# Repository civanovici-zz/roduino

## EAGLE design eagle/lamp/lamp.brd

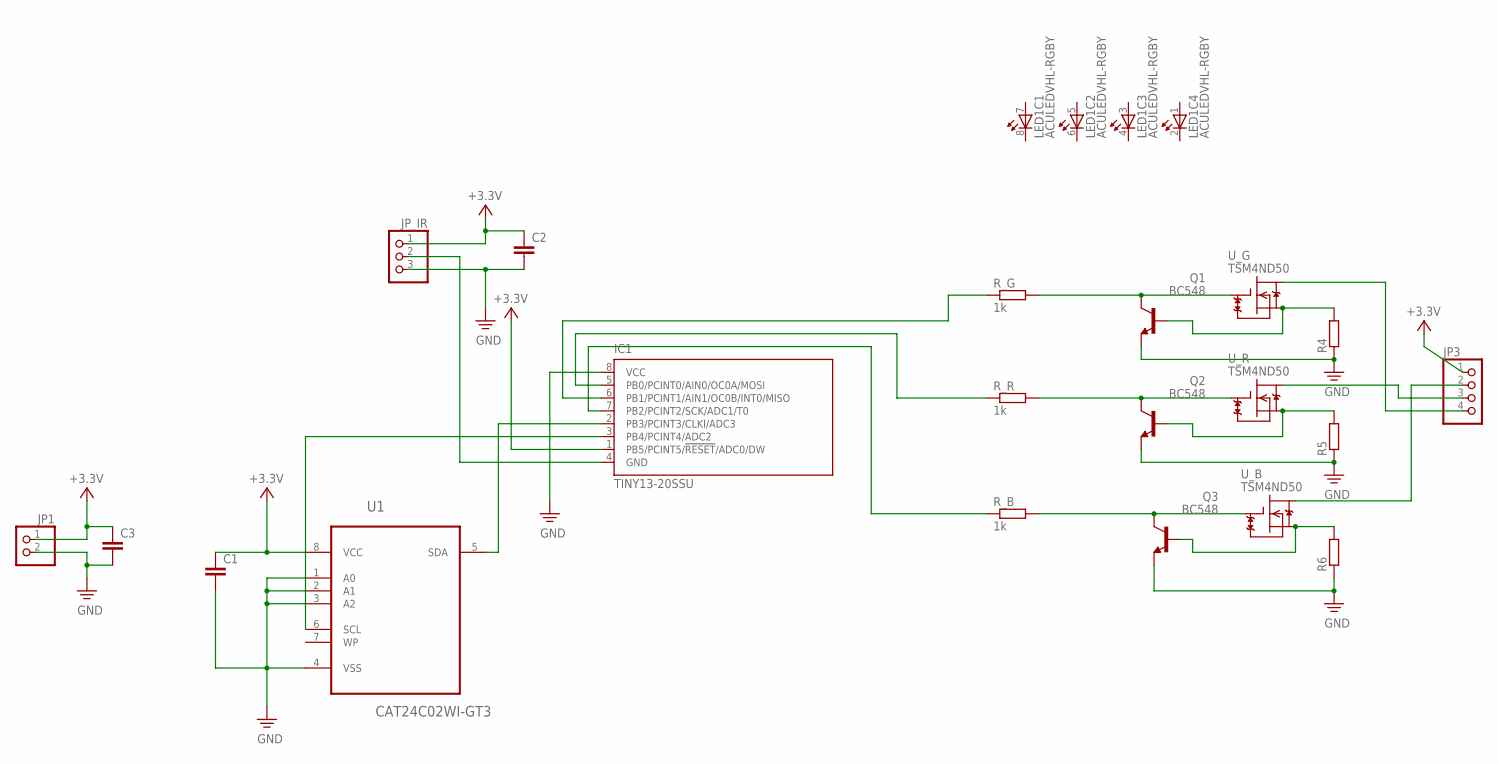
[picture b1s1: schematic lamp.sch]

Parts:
C1, C2, C3: C-EUC0805; C0805
IC1: TINY13-20SSU; 8S1
JP1: PINHD-1X2; 1X02
JP3: PINHD-1X4; 1X04
JP_IR: PINHD-1X3; 1X03
LED1: ACULEDVHL-RGBY; ACULEDVHL
Q1, Q2, Q3: BC548; TO92-EBC
R4, R5, R6: R-EU_0204/2V; 0204V
R_B: 1k; R0805
R_G: 1k; R0805
R_R: 1k; R0805
U1: CAT24C02WI-GT3; SOIC127P600X175-8N
U_B: TSM4ND50; TO252
U_G: TSM4ND50; TO252
U_R: TSM4ND50; TO252

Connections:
B: JP3.2, U_B.D
G: JP3.4, U_G.D
unnamed: IC1.2 (PB3/PCINT3/CLKI/ADC3), U1.5 (SDA)
unnamed: IC1.3 (PB4/PCINT4/ADC2), U1.6 (SCL)
unnamed: IC1.4 (GND), JP_IR.2
unnamed: Q1.C, R_G.2, U_G.G
unnamed: IC1.7 (PB2/PCINT2/SCK/ADC1/T0), R_B.1
unnamed: IC1.5 (PB0/PCINT0/AIN0/OC0A/MOSI), R_R.1
unnamed: IC1.6 (PB1/PCINT1/AIN1/OC0B/INT0/MISO), R_G.1
unnamed: Q1.B, R4.2, U_G.S
unnamed: Q2.C, R_R.2, U_R.G
unnamed: Q2.B, R5.2, U_R.S
unnamed: Q3.C, R_B.2, U_B.G
unnamed: Q3.B, R6.2, U_B.S
PE: C1.2, C2.2, C3.2, IC1.8 (VCC), JP1.2, JP_IR.3, Q1.E, Q2.E, Q3.E, R4.1, R5.1, R6.1, U1.1 (A0), U1.2 (A1), U1.3 (A2), U1.4 (VSS)
R: JP3.3, U_R.D
VCC: C1.1, C2.1, C3.1, IC1.1 (PB5/PCINT5/!RESET!/ADC0/DW), JP1.1, JP3.1, JP_IR.1, U1.8 (VCC)

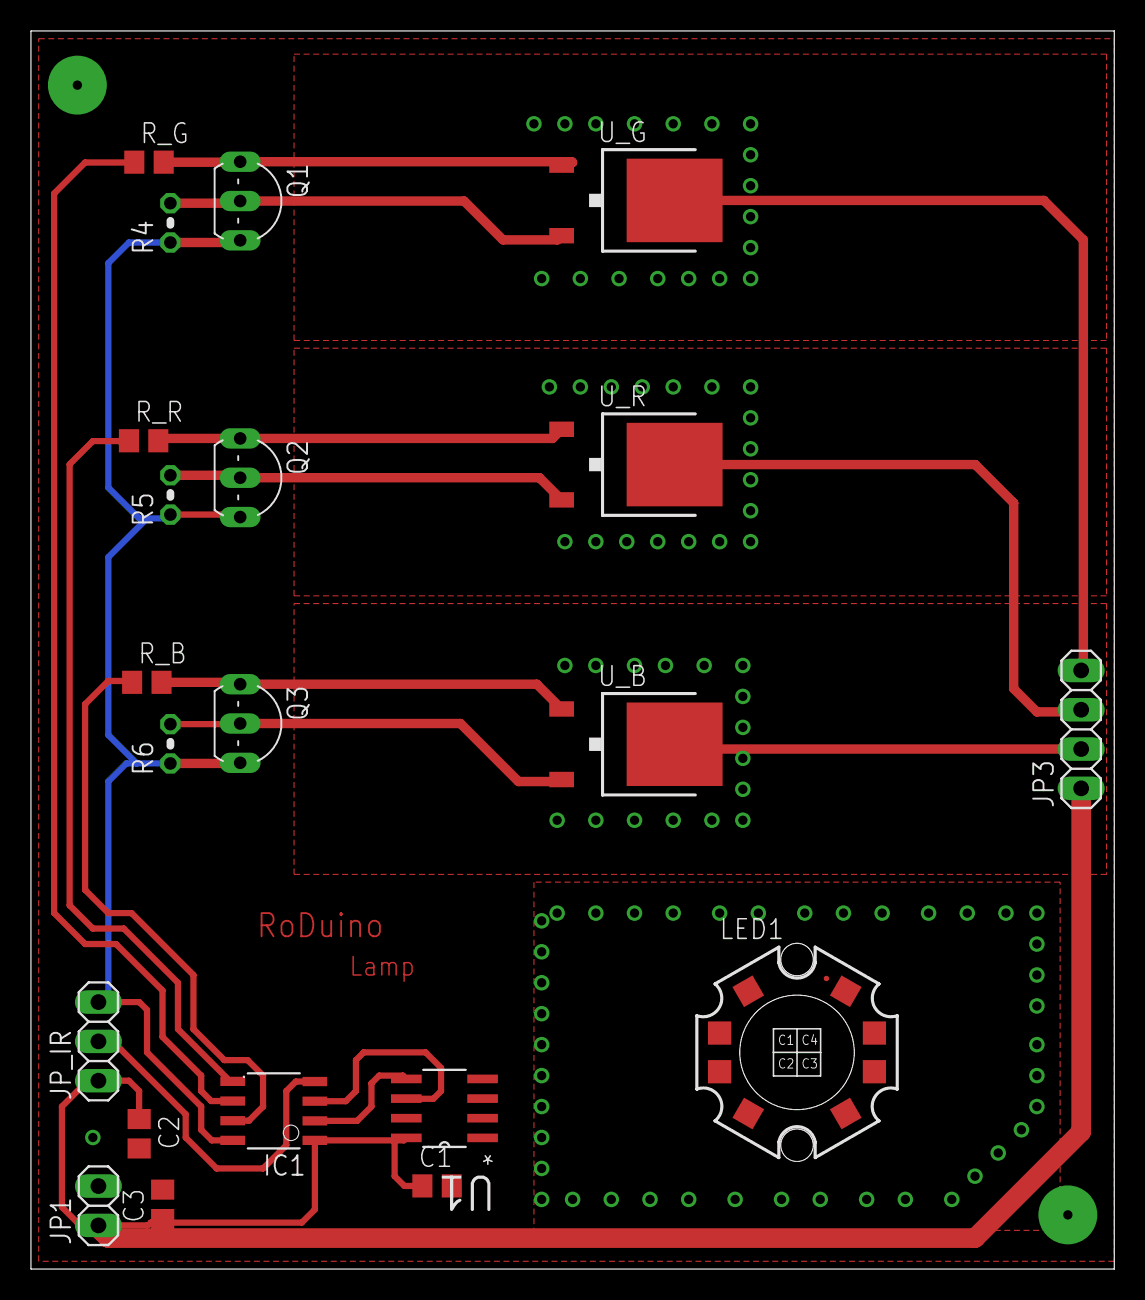
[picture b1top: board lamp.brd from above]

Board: 2 copper layers, 70.0 x 80.0 mm, 21 parts (0 on the bottom side), 17 nets.

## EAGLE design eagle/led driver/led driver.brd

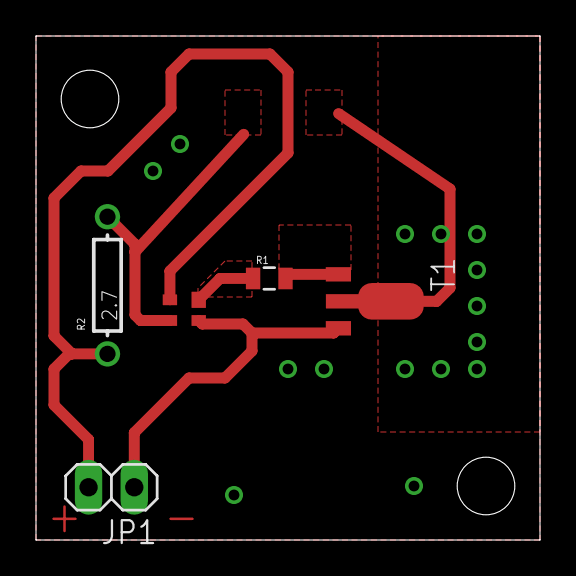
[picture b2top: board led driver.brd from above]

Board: 2 copper layers, 28.0 x 28.0 mm, 5 parts (0 on the bottom side), 5 nets.

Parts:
JP1: 1X02
R1: 220; 0805
R2: 2.7; AXIAL-0.3
T1: SOT89-BCE
U$9: BCR401W; SOT-343

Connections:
3.3V: JP1.2, R2.P$1, U$9.VSS
GND: JP1.1, T1.E, U$9.GND
unnamed: R1.2, T1.B
unnamed: R1.1, U$9.IOUT
unnamed: R2.P$2, U$9.REXT

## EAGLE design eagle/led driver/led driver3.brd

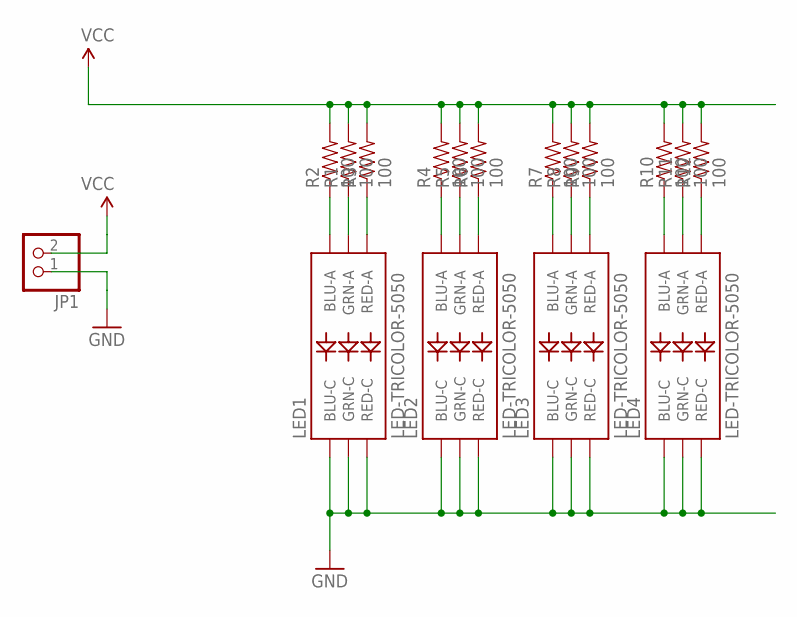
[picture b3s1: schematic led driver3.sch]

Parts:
JP1: PINHD-1X2; 1X02
LED1, LED2, LED3, LED4: LED-TRICOLOR-5050
R1, R2, R3, R4, R5, R6, R7, R8, R9, R10, R11, R12: 100; 0603-RES

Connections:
GND: JP1.1, LED1.4 (BLU-C), LED1.5 (RED-C), LED1.6 (GRN-C), LED2.4 (BLU-C), LED2.5 (RED-C), LED2.6 (GRN-C), LED3.4 (BLU-C), LED3.5 (RED-C), LED3.6 (GRN-C), LED4.4 (BLU-C), LED4.5 (RED-C), LED4.6 (GRN-C)
unnamed: LED2.3 (BLU-A), R4.1
unnamed: LED2.1 (GRN-A), R5.1
unnamed: LED2.2 (RED-A), R6.1
unnamed: LED3.3 (BLU-A), R7.1
unnamed: LED3.1 (GRN-A), R8.1
unnamed: LED3.2 (RED-A), R9.1
unnamed: LED4.3 (BLU-A), R10.1
unnamed: LED4.1 (GRN-A), R11.1
unnamed: LED4.2 (RED-A), R12.1
unnamed: LED1.3 (BLU-A), R2.1
unnamed: LED1.1 (GRN-A), R1.1
unnamed: LED1.2 (RED-A), R3.1
VCC: JP1.2, R1.2, R2.2, R3.2, R4.2, R5.2, R6.2, R7.2, R8.2, R9.2, R10.2, R11.2, R12.2

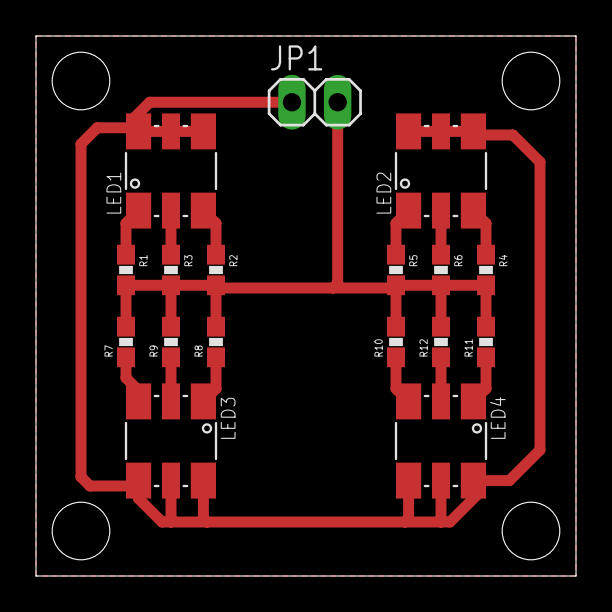
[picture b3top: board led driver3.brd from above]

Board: 2 copper layers, 30.0 x 30.0 mm, 17 parts (0 on the bottom side), 14 nets.

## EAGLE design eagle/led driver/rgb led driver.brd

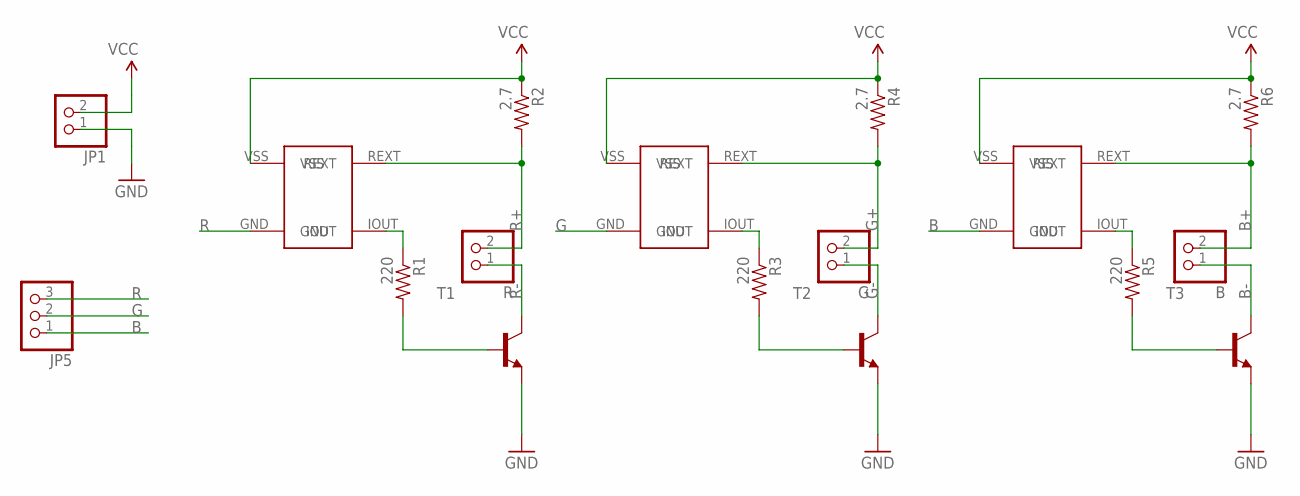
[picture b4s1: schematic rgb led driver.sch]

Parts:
B: PINHD-1X2; 1X02
G: PINHD-1X2; 1X02
JP1: PINHD-1X2; 1X02
JP5: PINHD-1X3; 1X03
R: PINHD-1X2; 1X02
R1, R3, R5: 220; 0805
R2, R4, R6: 2.7; AXIAL-0.3
T1, T2, T3: -NPN-SOT89-BCE; SOT89-BCE
U$1, U$2, U$9: BCR401W; SOT-343

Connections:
3.3V: JP1.2, R2.P$1 (1), R4.P$1 (1), R6.P$1 (1), U$1.VSS, U$2.VSS, U$9.VSS
B: JP5.1, U$2.GND
B+: B.2, R6.P$2 (2), U$2.REXT
B-: B.1, T3.C
G: JP5.2, U$1.GND
G+: G.2, R4.P$2 (2), U$1.REXT
G-: G.1, T2.C
GND: JP1.1, T1.E, T2.E, T3.E
unnamed: R1.2, T1.B
unnamed: R3.1, U$1.IOUT
unnamed: R3.2, T2.B
unnamed: R5.1, U$2.IOUT
unnamed: R5.2, T3.B
unnamed: R1.1, U$9.IOUT
R: JP5.3, U$9.GND
R+: R.2, R2.P$2 (2), U$9.REXT
R-: R.1, T1.C

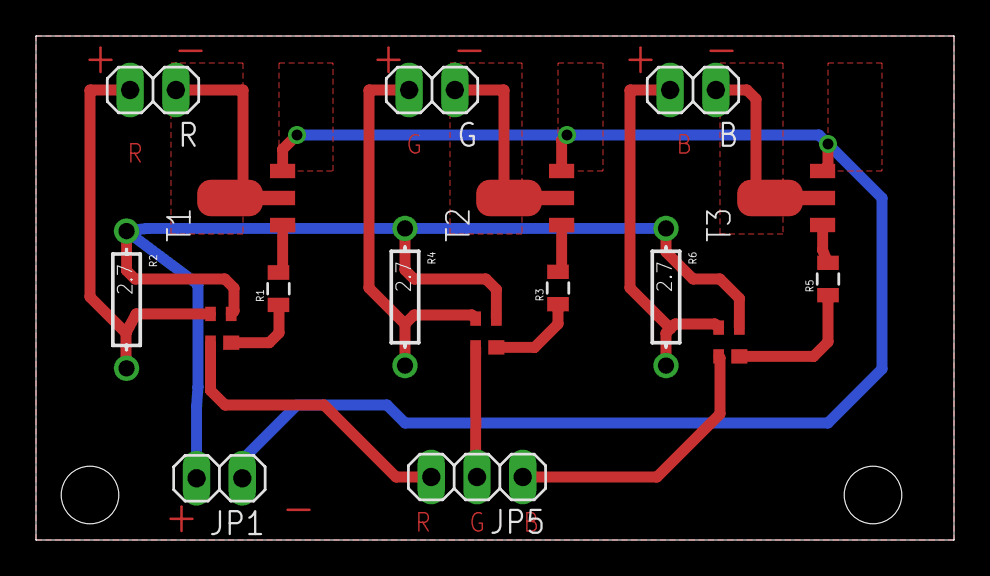
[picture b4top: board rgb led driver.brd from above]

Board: 2 copper layers, 51.0 x 28.0 mm, 17 parts (0 on the bottom side), 17 nets.

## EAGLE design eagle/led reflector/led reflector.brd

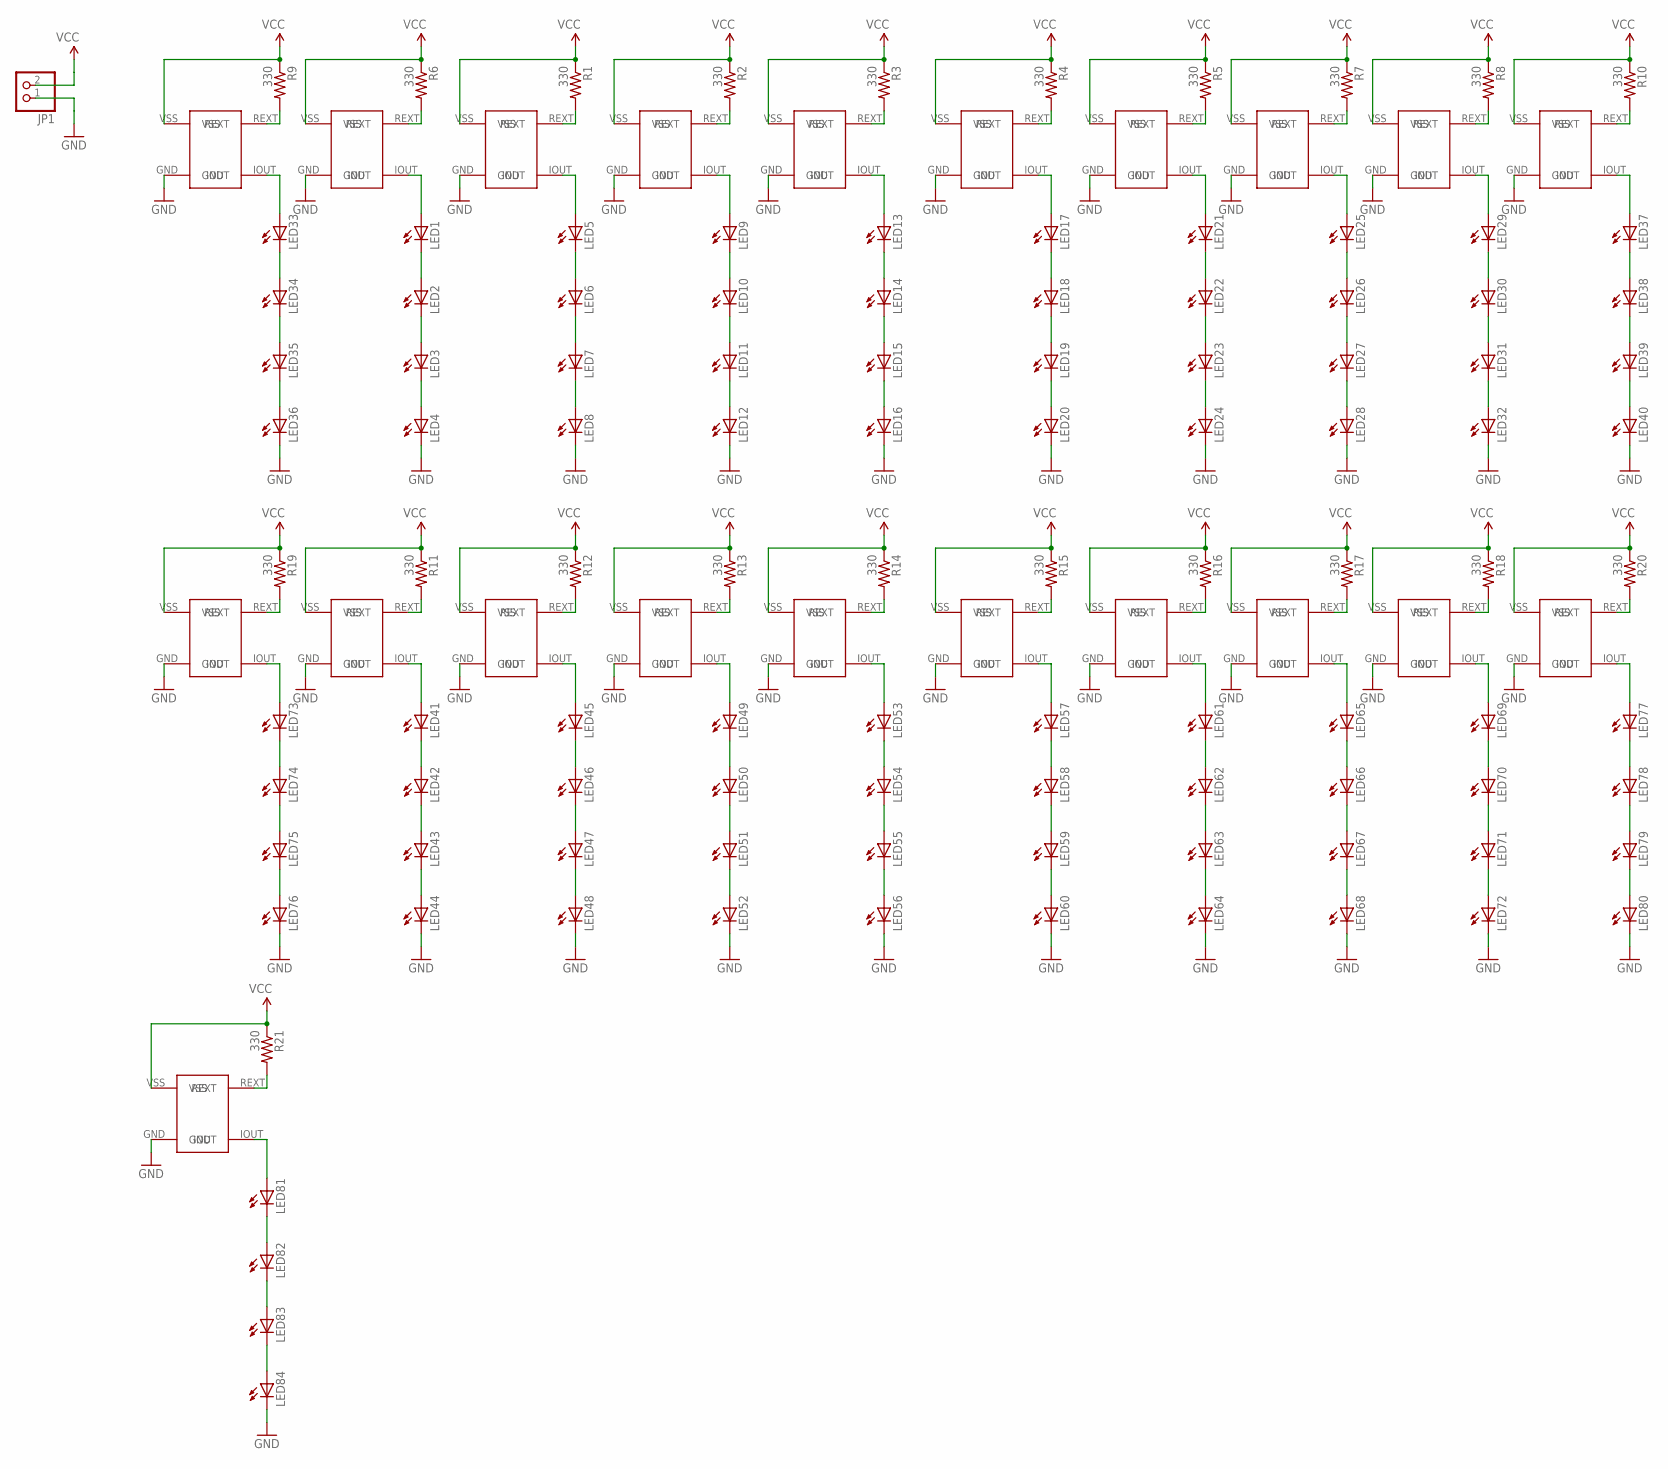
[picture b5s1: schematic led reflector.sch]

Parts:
JP1: PINHD-1X2; 1X02
LED1, LED2, LED3, LED4, LED5, LED6, LED7, LED8, LED9, LED10, LED11, LED12, LED13, LED14, LED15, LED16, LED17, LED18, LED19, LED20, LED21, LED22, LED23, LED24, LED25, LED26, LED27, LED28, LED29, LED30, LED31, LED32, LED33, LED34, LED35, LED36, LED37, LED38, LED39, LED40, LED41, LED42, LED43, LED44, LED45, LED46, LED47, LED48, LED49, LED50, LED51, LED52, LED53, LED54, LED55, LED56, LED57, LED58, LED59, LED60, LED61, LED62, LED63, LED64, LED65, LED66, LED67, LED68, LED69, LED70, LED71, LED72, LED73, LED74, LED75, LED76, LED77, LED78, LED79, LED80, LED81, LED82, LED83, LED84: LED5MM
R1, R2, R3, R4, R5, R6, R7, R8, R9, R10, R11, R12, R13, R14, R15, R16, R17, R18, R19, R20, R21: 330; 0805
U$1, U$2, U$3, U$4, U$5, U$6, U$7, U$8, U$9, U$10, U$11, U$12, U$13, U$14, U$15, U$16, U$17, U$18, U$19, U$20, U$21: BCR401W; SOT-343

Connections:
3.3V: JP1.2, R1.1, R2.1, R3.1, R4.1, R5.1, R6.1, R7.1, R8.1, R9.1, R10.1, R11.1, R12.1, R13.1, R14.1, R15.1, R16.1, R17.1, R18.1, R19.1, R20.1, R21.1, U$1.VSS, U$2.VSS, U$3.VSS, U$4.VSS, U$5.VSS, U$6.VSS, U$7.VSS, U$8.VSS, U$9.VSS, U$10.VSS, U$11.VSS, U$12.VSS, U$13.VSS, U$14.VSS, U$15.VSS, U$16.VSS, U$17.VSS, U$18.VSS, U$19.VSS, U$20.VSS, U$21.VSS
GND: JP1.1, LED4.K (C), LED8.K (C), LED12.K (C), LED16.K (C), LED20.K (C), LED24.K (C), LED28.K (C), LED32.K (C), LED36.K (C), LED40.K (C), LED44.K (C), LED48.K (C), LED52.K (C), LED56.K (C), LED60.K (C), LED64.K (C), LED68.K (C), LED72.K (C), LED76.K (C), LED80.K (C), LED84.K (C), U$1.GND, U$2.GND, U$3.GND, U$4.GND, U$5.GND, U$6.GND, U$7.GND, U$8.GND, U$9.GND, U$10.GND, U$11.GND, U$12.GND, U$13.GND, U$14.GND, U$15.GND, U$16.GND, U$17.GND, U$18.GND, U$19.GND, U$20.GND, U$21.GND
unnamed: LED1.A, U$1.IOUT
unnamed: LED1.K (C), LED2.A
unnamed: LED2.K (C), LED3.A
unnamed: LED3.K (C), LED4.A
unnamed: R6.2, U$1.REXT
unnamed: LED41.A, U$11.IOUT
unnamed: LED5.A, U$2.IOUT
unnamed: LED5.K (C), LED6.A
unnamed: LED6.K (C), LED7.A
unnamed: LED7.K (C), LED8.A
unnamed: R1.2, U$2.REXT
unnamed: LED9.A, U$3.IOUT
unnamed: LED9.K (C), LED10.A
unnamed: LED10.K (C), LED11.A
unnamed: LED11.K (C), LED12.A
unnamed: R2.2, U$3.REXT
unnamed: LED13.A, U$4.IOUT
unnamed: LED13.K (C), LED14.A
unnamed: LED14.K (C), LED15.A
unnamed: LED15.K (C), LED16.A
unnamed: R3.2, U$4.REXT
unnamed: LED17.A, U$5.IOUT
unnamed: LED17.K (C), LED18.A
unnamed: LED18.K (C), LED19.A
unnamed: LED19.K (C), LED20.A
unnamed: R4.2, U$5.REXT
unnamed: LED21.A, U$6.IOUT
unnamed: LED21.K (C), LED22.A
unnamed: LED22.K (C), LED23.A
unnamed: LED23.K (C), LED24.A
unnamed: R5.2, U$6.REXT
unnamed: LED25.A, U$7.IOUT
unnamed: LED25.K (C), LED26.A
unnamed: LED26.K (C), LED27.A
unnamed: LED27.K (C), LED28.A
unnamed: R7.2, U$7.REXT
unnamed: LED29.A, U$8.IOUT
unnamed: LED29.K (C), LED30.A
unnamed: LED30.K (C), LED31.A
unnamed: LED31.K (C), LED32.A
unnamed: R8.2, U$8.REXT
unnamed: LED33.A, U$9.IOUT
unnamed: LED33.K (C), LED34.A
unnamed: LED34.K (C), LED35.A
unnamed: LED35.K (C), LED36.A
unnamed: R9.2, U$9.REXT
unnamed: LED37.A, U$10.IOUT
unnamed: LED37.K (C), LED38.A
unnamed: LED38.K (C), LED39.A
unnamed: LED39.K (C), LED40.A
unnamed: R10.2, U$10.REXT
unnamed: LED41.K (C), LED42.A
unnamed: LED42.K (C), LED43.A
unnamed: LED43.K (C), LED44.A
unnamed: R11.2, U$11.REXT
unnamed: LED45.A, U$12.IOUT
unnamed: LED45.K (C), LED46.A
unnamed: LED46.K (C), LED47.A
unnamed: LED47.K (C), LED48.A
unnamed: R12.2, U$12.REXT
unnamed: LED49.A, U$13.IOUT
unnamed: LED49.K (C), LED50.A
unnamed: LED50.K (C), LED51.A
unnamed: LED51.K (C), LED52.A
unnamed: R13.2, U$13.REXT
unnamed: LED53.A, U$14.IOUT
unnamed: LED53.K (C), LED54.A
unnamed: LED54.K (C), LED55.A
unnamed: LED55.K (C), LED56.A
unnamed: R14.2, U$14.REXT
unnamed: LED57.A, U$15.IOUT
unnamed: LED57.K (C), LED58.A
unnamed: LED58.K (C), LED59.A
unnamed: LED59.K (C), LED60.A
unnamed: R15.2, U$15.REXT
unnamed: LED61.A, U$16.IOUT
unnamed: LED61.K (C), LED62.A
unnamed: LED62.K (C), LED63.A
unnamed: LED63.K (C), LED64.A
unnamed: R16.2, U$16.REXT
unnamed: LED65.A, U$17.IOUT
unnamed: LED65.K (C), LED66.A
unnamed: LED66.K (C), LED67.A
unnamed: LED67.K (C), LED68.A
unnamed: R17.2, U$17.REXT
unnamed: LED69.A, U$18.IOUT
unnamed: LED69.K (C), LED70.A
unnamed: LED70.K (C), LED71.A
unnamed: LED71.K (C), LED72.A
unnamed: R18.2, U$18.REXT
unnamed: LED73.A, U$19.IOUT
unnamed: LED73.K (C), LED74.A
unnamed: LED74.K (C), LED75.A
unnamed: LED75.K (C), LED76.A
unnamed: R19.2, U$19.REXT
unnamed: LED77.A, U$20.IOUT
unnamed: LED77.K (C), LED78.A
unnamed: LED78.K (C), LED79.A
unnamed: LED79.K (C), LED80.A
unnamed: R20.2, U$20.REXT
unnamed: LED81.A, U$21.IOUT
unnamed: LED81.K (C), LED82.A
unnamed: LED82.K (C), LED83.A
unnamed: LED83.K (C), LED84.A
unnamed: R21.2, U$21.REXT

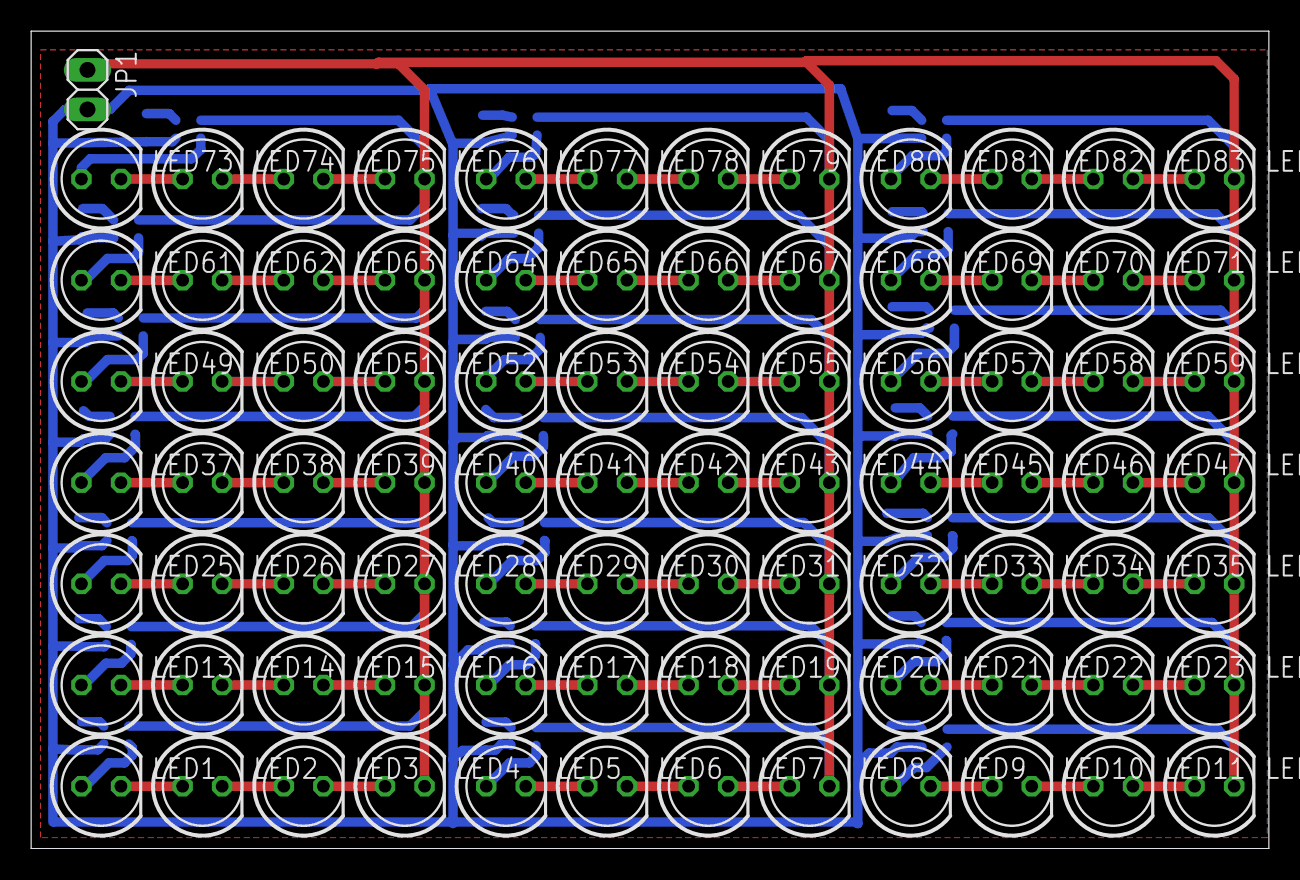
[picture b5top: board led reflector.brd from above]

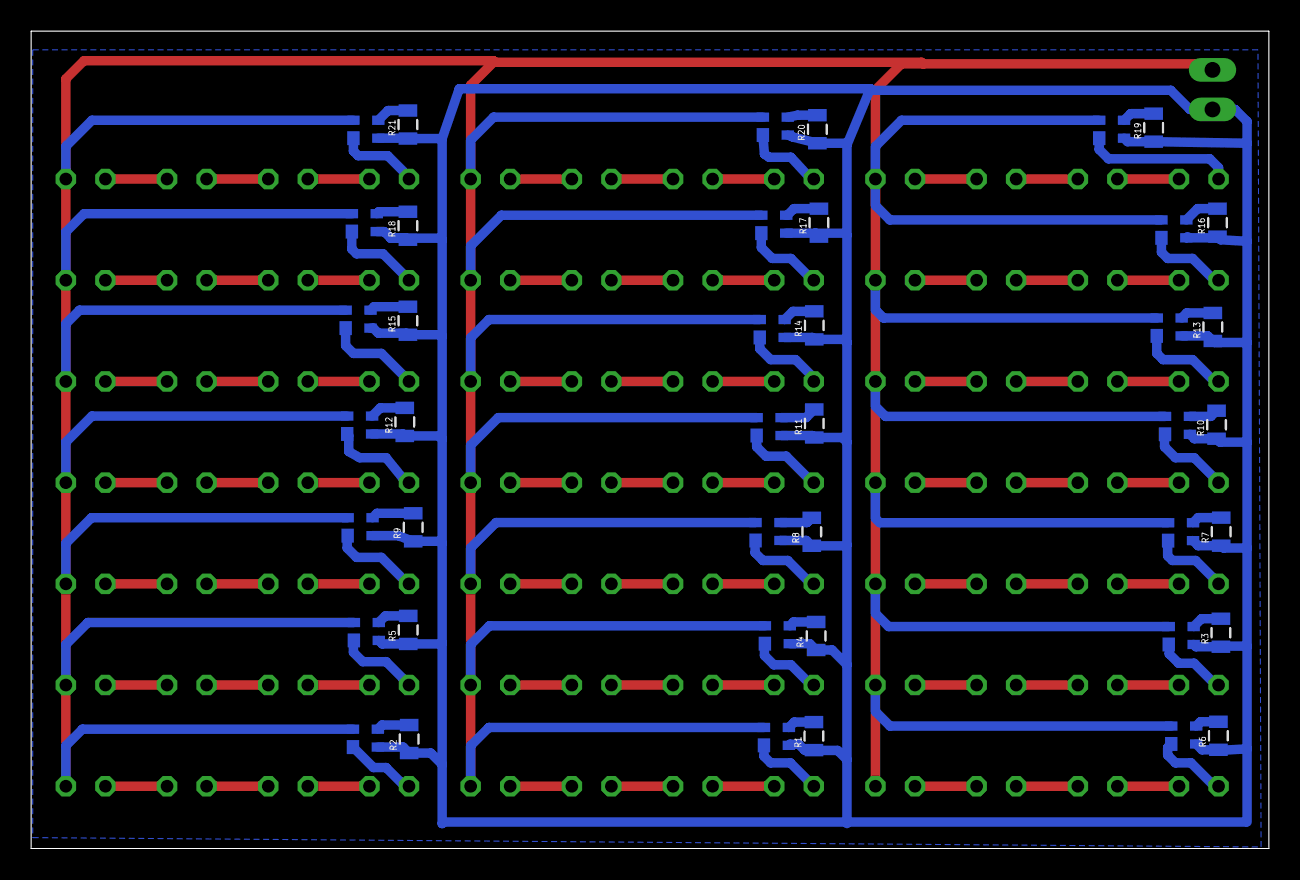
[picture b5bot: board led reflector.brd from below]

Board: 2 copper layers, 79.5 x 52.5 mm, 127 parts (42 on the bottom side), 107 nets.

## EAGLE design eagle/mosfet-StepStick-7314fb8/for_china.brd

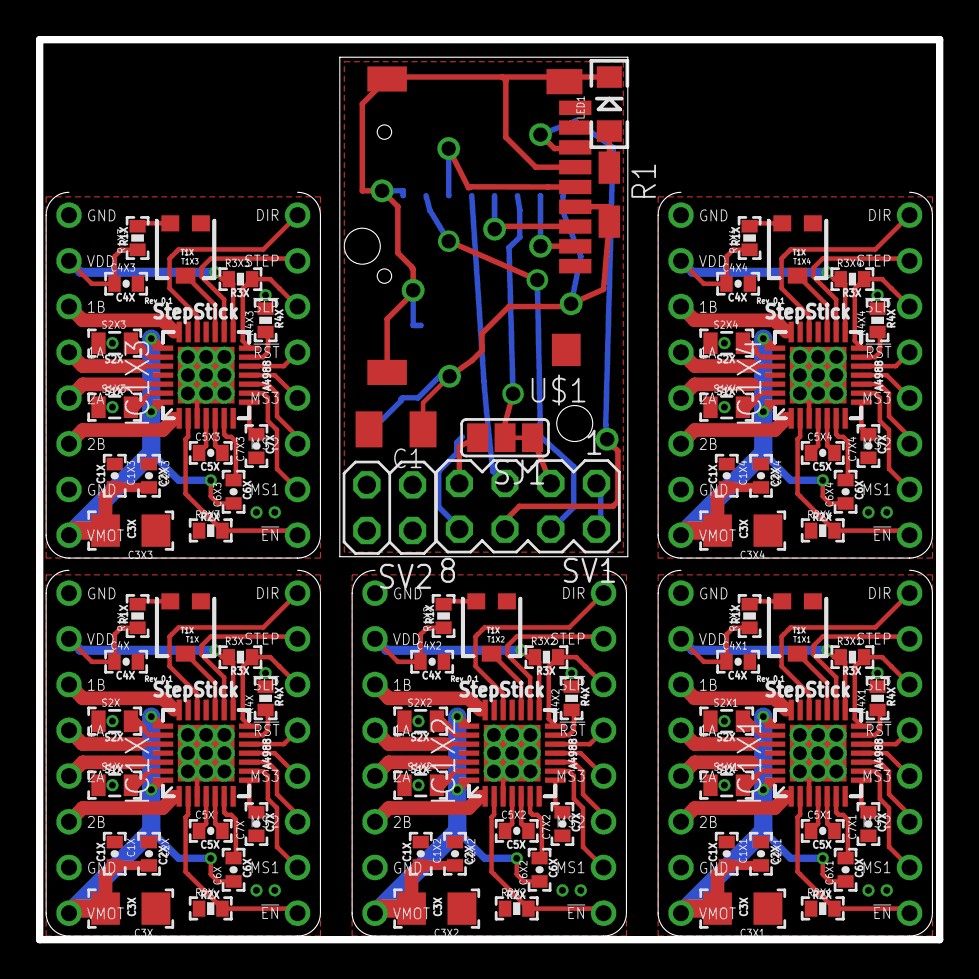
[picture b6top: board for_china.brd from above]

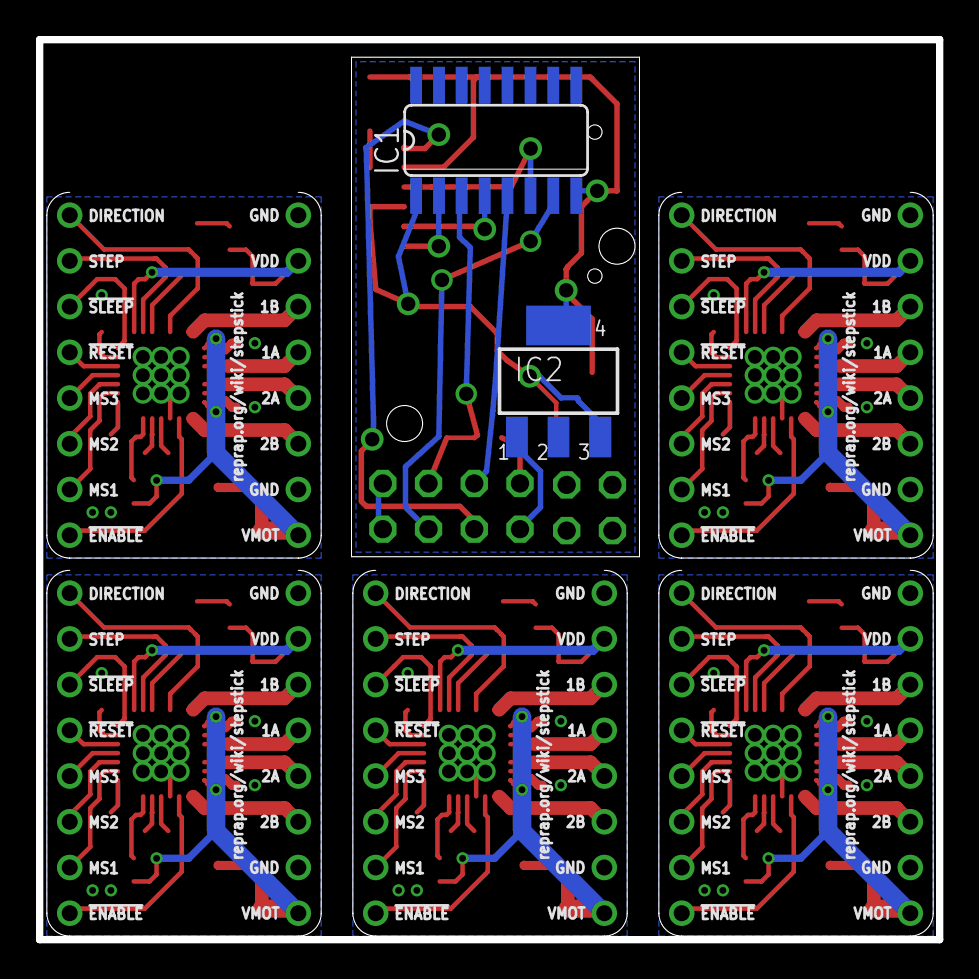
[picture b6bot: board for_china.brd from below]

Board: 2 copper layers, 50.0 x 50.0 mm, 89 parts (2 on the bottom side), 132 nets.

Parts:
C1: C1206K
C1X, C1X1, C1X2, C1X3, C1X4, C2X, C2X1, C2X2, C2X3, C2X4, C5X, C5X1, C5X2, C5X3, C5X4, C6X, C6X1, C6X2, C6X3, C6X4: .1uf; 0402-CAP
C3X, C3X1, C3X2, C3X3, C3X4: 4.7uF; 1206
C4X, C4X1, C4X2, C4X3, C4X4, C7X, C7X1, C7X2, C7X3, C7X4: .22uf; 0402-CAP
IC1: 4050D; SO16
IC1X, IC1X1, IC1X2, IC1X3, IC1X4: A4988; QFN28ET
IC2: LM340MP-05; SOT223
J1X, J1X1, J1X2, J1X3, J1X4: CLONOLU
LED1: LED-1206
R1: R1206W
R1X, R1X1, R1X2, R1X3, R1X4: 20k; 0402-RES
R2X, R2X1, R2X2, R2X3, R2X4, R3X, R3X1, R3X2, R3X3, R3X4: 100k; 0402-RES
R4X, R4X1, R4X2, R4X3, R4X4: 10k; 0402-RES
S1X, S1X1, S1X2, S1X3, S1X4, S2X, S2X1, S2X2, S2X3, S2X4: 0.2; 0805
SJ1: SJ_2
SV1: MA04-2
SV2: 2X02
T1X, T1X1, T1X2, T1X3, T1X4: TRIM; TRIMPOT-3MM
U$1: MICROSD_PP

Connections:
GND: C1X.1, C2X.1, C3X.1, C4X.2, C7X.1, IC1X.3, IC1X.7, IC1X.18, IC1X.20, IC1X.25, IC1X.EXP, J1X.GND$1, J1X.GND$2, R2X.1, R4X.2, S1X.1, S2X.1, T1X.1
GND1: C1X1.1, C2X1.1, C3X1.1, C4X1.2, C7X1.1, IC1X1.3, IC1X1.7, IC1X1.18, IC1X1.20, IC1X1.25, IC1X1.EXP, J1X1.GND$1, J1X1.GND$2, R2X1.1, R4X1.2, S1X1.1, S2X1.1, T1X1.1
GND2: C1X2.1, C2X2.1, C3X2.1, C4X2.2, C7X2.1, IC1X2.3, IC1X2.7, IC1X2.18, IC1X2.20, IC1X2.25, IC1X2.EXP, J1X2.GND$1, J1X2.GND$2, R2X2.1, R4X2.2, S1X2.1, S2X2.1, T1X2.1
GND3: C1X3.1, C2X3.1, C3X3.1, C4X3.2, C7X3.1, IC1X3.3, IC1X3.7, IC1X3.18, IC1X3.20, IC1X3.25, IC1X3.EXP, J1X3.GND$1, J1X3.GND$2, R2X3.1, R4X3.2, S1X3.1, S2X3.1, T1X3.1
GND4: C1.2, IC1.8, IC2.4, LED1.C, SV1.1, SV1.2, U$1.6, U$1.GND@1, U$1.GND@2, U$1.GND@3, U$1.GND@4
GND5: C1X4.1, C2X4.1, C3X4.1, C4X4.2, C7X4.1, IC1X4.3, IC1X4.7, IC1X4.18, IC1X4.20, IC1X4.25, IC1X4.EXP, J1X4.GND$1, J1X4.GND$2, R2X4.1, R4X4.2, S1X4.1, S2X4.1, T1X4.1
unnamed: IC1.2, U$1.2
unnamed: IC1.4, U$1.3
unnamed: IC1.6, U$1.5
unnamed: SV1.6, U$1.7
unnamed: SJ1.3, SV1.7
unnamed: IC1.3, SJ1.1, SJ1.2, SV1.3
unnamed: IC1.7, SV1.4
unnamed: IC1.5, SV1.5
unnamed: IC2.1, SV1.8
unnamed: LED1.A, R1.1
VCC: C1.1, IC1.1, IC2.3, R1.2, U$1.4
VDD: C4X.1, IC1X.15, J1X.VDD, R1X.1, R3X.1
VDD1: C4X1.1, IC1X1.15, J1X1.VDD, R1X1.1, R3X1.1
VDD2: C4X2.1, IC1X2.15, J1X2.VDD, R1X2.1, R3X2.1
VDD3: C4X3.1, IC1X3.15, J1X3.VDD, R1X3.1, R3X3.1
VDD4: C4X4.1, IC1X4.15, J1X4.VDD, R1X4.1, R3X4.1
VMOT: C1X.2, C2X.2, C3X.2, C6X.1, IC1X.22, IC1X.28, J1X.VMOT
VMOT1: C1X1.2, C2X1.2, C3X1.2, C6X1.1, IC1X1.22, IC1X1.28, J1X1.VMOT
VMOT2: C1X2.2, C2X2.2, C3X2.2, C6X2.1, IC1X2.22, IC1X2.28, J1X2.VMOT
VMOT3: C1X3.2, C2X3.2, C3X3.2, C6X3.1, IC1X3.22, IC1X3.28, J1X3.VMOT
VMOT4: C1X4.2, C2X4.2, C3X4.2, C6X4.1, IC1X4.22, IC1X4.28, J1X4.VMOT
XCP1: C5X.1, IC1X.4
XCP2: C5X.2, IC1X.5
XCP3: C5X1.1, IC1X1.4
XCP4: C5X1.2, IC1X1.5
XCP5: C5X2.1, IC1X2.4
XCP6: C5X2.2, IC1X2.5
XCP7: C5X3.1, IC1X3.4
XCP8: C5X3.2, IC1X3.5
XCP9: C5X4.1, IC1X4.4
XCP10: C5X4.2, IC1X4.5
XDIR: IC1X.19, J1X.DIR
XDIR1: IC1X1.19, J1X1.DIR
XDIR2: IC1X2.19, J1X2.DIR
XDIR3: IC1X3.19, J1X3.DIR
XDIR4: IC1X4.19, J1X4.DIR
XENABLE: IC1X.2, J1X.!EN, R2X.2
XENABLE1: IC1X1.2, J1X1.!EN, R2X1.2
XENABLE2: IC1X2.2, J1X2.!EN, R2X2.2
XENABLE3: IC1X3.2, J1X3.!EN, R2X3.2
XENABLE4: IC1X4.2, J1X4.!EN, R2X4.2
XMS1: IC1X.9, J1X.MS1
XMS2: IC1X.10, J1X.MS2
XMS3: IC1X.11, J1X.MS3
XMS4: IC1X1.9, J1X1.MS1
XMS5: IC1X1.10, J1X1.MS2
XMS6: IC1X1.11, J1X1.MS3
XMS7: IC1X2.9, J1X2.MS1
XMS8: IC1X2.10, J1X2.MS2
XMS9: IC1X2.11, J1X2.MS3
XMS10: IC1X3.9, J1X3.MS1
XMS11: IC1X3.10, J1X3.MS2
XMS12: IC1X3.11, J1X3.MS3
XMS13: IC1X4.9, J1X4.MS1
XMS14: IC1X4.10, J1X4.MS2
XMS15: IC1X4.11, J1X4.MS3
XOUT1A: IC1X.24, J1X.1A
XOUT1A1: IC1X1.24, J1X1.1A
XOUT1A2: IC1X2.24, J1X2.1A
XOUT1A3: IC1X3.24, J1X3.1A
XOUT1A4: IC1X4.24, J1X4.1A
XOUT1B: IC1X.21, J1X.1B
XOUT1B1: IC1X1.21, J1X1.1B
XOUT1B2: IC1X2.21, J1X2.1B
XOUT1B3: IC1X3.21, J1X3.1B
XOUT1B4: IC1X4.21, J1X4.1B
XOUT2A: IC1X.26, J1X.2A
XOUT2A1: IC1X1.26, J1X1.2A
XOUT2A2: IC1X2.26, J1X2.2A
XOUT2A3: IC1X3.26, J1X3.2A
XOUT2A4: IC1X4.26, J1X4.2A
XOUT2B: IC1X.1, J1X.2B
XOUT2B1: IC1X1.1, J1X1.2B
XOUT2B2: IC1X2.1, J1X2.2B
XOUT2B3: IC1X3.1, J1X3.2B
XOUT2B4: IC1X4.1, J1X4.2B
XREF: IC1X.17, T1X.2
XREF1: IC1X1.17, T1X1.2
XREF2: R1X.2, T1X.3
XREF3: R1X1.2, T1X1.3
XREF4: IC1X2.17, T1X2.2
XREF5: R1X2.2, T1X2.3
XREF6: IC1X3.17, T1X3.2
XREF7: R1X3.2, T1X3.3
XREF8: IC1X4.17, T1X4.2
XREF9: R1X4.2, T1X4.3
XRESET: IC1X.12, J1X.!RST
XRESET1: IC1X1.12, J1X1.!RST
XRESET2: IC1X2.12, J1X2.!RST
XRESET3: IC1X3.12, J1X3.!RST
XRESET4: IC1X4.12, J1X4.!RST
XROSC: IC1X.13, R4X.1
XROSC1: IC1X1.13, R4X1.1
XROSC2: IC1X2.13, R4X2.1
XROSC3: IC1X3.13, R4X3.1
XROSC4: IC1X4.13, R4X4.1
XSENSE1: IC1X.23, S2X.2
XSENSE2: IC1X.27, S1X.2
XSENSE3: IC1X1.27, S1X1.2
XSENSE4: IC1X1.23, S2X1.2
XSENSE5: IC1X2.27, S1X2.2
XSENSE6: IC1X2.23, S2X2.2
XSENSE7: IC1X3.27, S1X3.2
XSENSE8: IC1X3.23, S2X3.2
XSENSE9: IC1X4.27, S1X4.2
XSENSE10: IC1X4.23, S2X4.2
XSLEEP: IC1X.14, J1X.!SLP, R3X.2
XSLEEP1: IC1X1.14, J1X1.!SLP, R3X1.2
XSLEEP2: IC1X2.14, J1X2.!SLP, R3X2.2
XSLEEP3: IC1X3.14, J1X3.!SLP, R3X3.2
XSLEEP4: IC1X4.14, J1X4.!SLP, R3X4.2
XSTEP: IC1X.16, J1X.STEP
XSTEP1: IC1X1.16, J1X1.STEP
XSTEP2: IC1X2.16, J1X2.STEP
XSTEP3: IC1X3.16, J1X3.STEP
XSTEP4: IC1X4.16, J1X4.STEP
XVCP: C6X.2, IC1X.6
XVCP1: C6X1.2, IC1X1.6
XVCP2: C6X2.2, IC1X2.6
XVCP3: C6X3.2, IC1X3.6
XVCP4: C6X4.2, IC1X4.6
XVREG: C7X.2, IC1X.8
XVREG1: C7X1.2, IC1X1.8
XVREG2: C7X2.2, IC1X2.8
XVREG3: C7X3.2, IC1X3.8
XVREG4: C7X4.2, IC1X4.8
